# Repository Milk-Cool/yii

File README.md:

# yii
tomodachi life-style mii dolls with esp32's inside that can speak to each other via BLE and TTS!

## how do i use it?
first, you need to build the dolls!! you can find the pcb files and the schematic under the `kicad/` directory, or you can take a look at them here:

note that even though i'd recommend a pcb, it's not really necessary to use a pcb since all the components are held together by plush anyway. you can also see a list of components in `bom.csv`.\
as for the dolls themselves, go creative! i found [these on aliexpress](https://www.aliexpress.us/item/3256811798258951.html), and dyed them with fabric paint. i also glued on velcro with fabric glue for attaching the facial features (`face/` for files to be printed), and used a zip locker so that i can open and close them to take components out when needed.

after you're done with the physical part, install the firmware on your esp32's (can be found in `firmware/`)
you can use the [online tool](https://milk-cool.github.io/yii/) to set up the dolls' name and wifi password via usb, then connect via wifi, set voice parameters and reboot to doll mode! (note: if anything goes wrong and the dolls end up bricked, you can erase the flash with esptool, google it)

as for the remote, you're gonna need a plain esp32 board. just flash it with the same firmware and set it up like you'd set up a doll, but reboot it to control mode instead. then, using the online tool, you can control your dolls (poke, feed, and play with them).

## what does it do?
there's a lot of stuff you can do with the dolls, but the most important one is watching them!! if you get two or more of them, you can watch them talk to each other. they'll develop a friendship and maybe even a romantic relationship eventually! (note: there's no gender/romantic preferences system here, everyone's attracted to everyone)

other than that, you can feed them with the remote, poke them, or play games with them. you can also track their progress and their XP as they talk to others more and more.

## why does this exist?
i was a really big fan of tomodachi life ever since i learned about the first game, and i thought i might want to bring the concept of miis to life!! and so i did :D

it's nowhere near as good, obviously, but i'm happy with the result

## credits
1p2t kicad library: https://github.com/BrianLeishman/jrgbwww24/blob/master/1P2T%20SPDT.kicad_mod
tp4056 kicad library: https://github.com/ccadic/TP4056-18650

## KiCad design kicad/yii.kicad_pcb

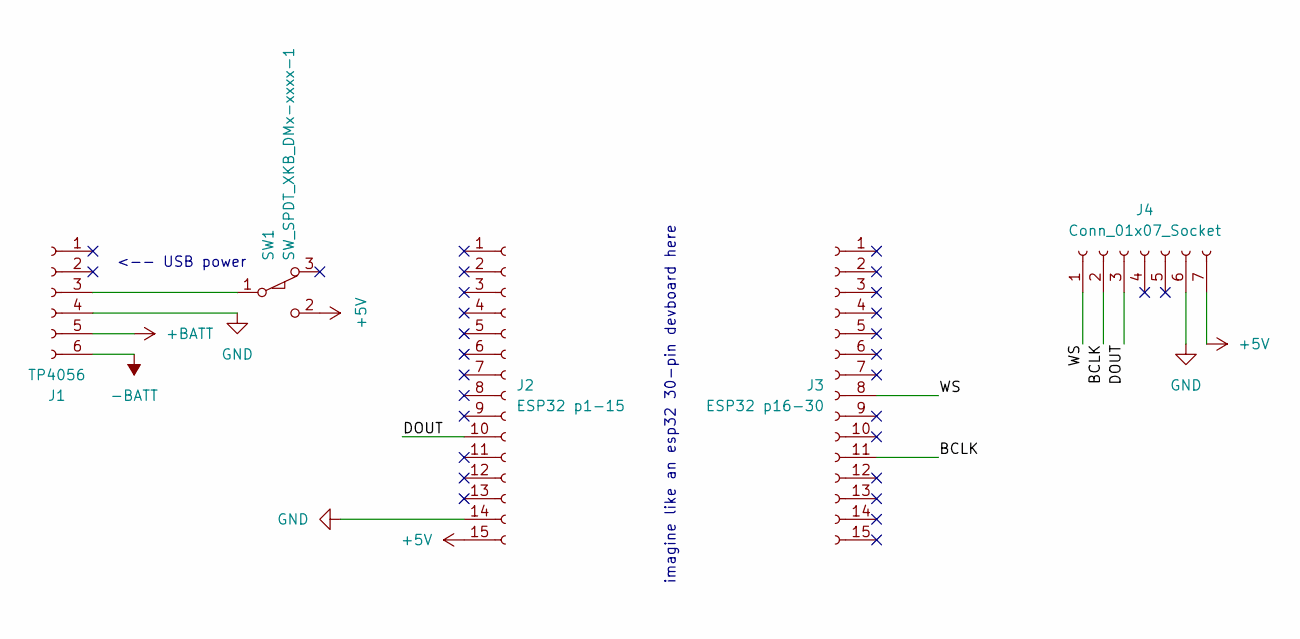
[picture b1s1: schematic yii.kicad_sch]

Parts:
J1: TP4056; TP4056-18650
J2: ESP32 p1-15; PinHeader_1x15_P2.54mm_Vertical
J3: ESP32 p16-30; PinHeader_1x15_P2.54mm_Vertical
J4: Conn_01x07_Socket; PinSocket_1x07_P2.54mm_Vertical
SW1: SW_SPDT_XKB_DMx-xxxx-1; 1p2t

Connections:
+5V: J2.15, J4.7, SW1.2 (B)
+BATT: J1.5
-BATT: J1.6
/BCLK: J3.11, J4.2
/DOUT: J2.10, J4.3
/WS: J3.8, J4.1
GND: J1.4, J2.14, J4.6
unnamed: J1.3, SW1.1 (A)

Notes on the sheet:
<-- USB power
imagine like an esp32 30-pin devboard here

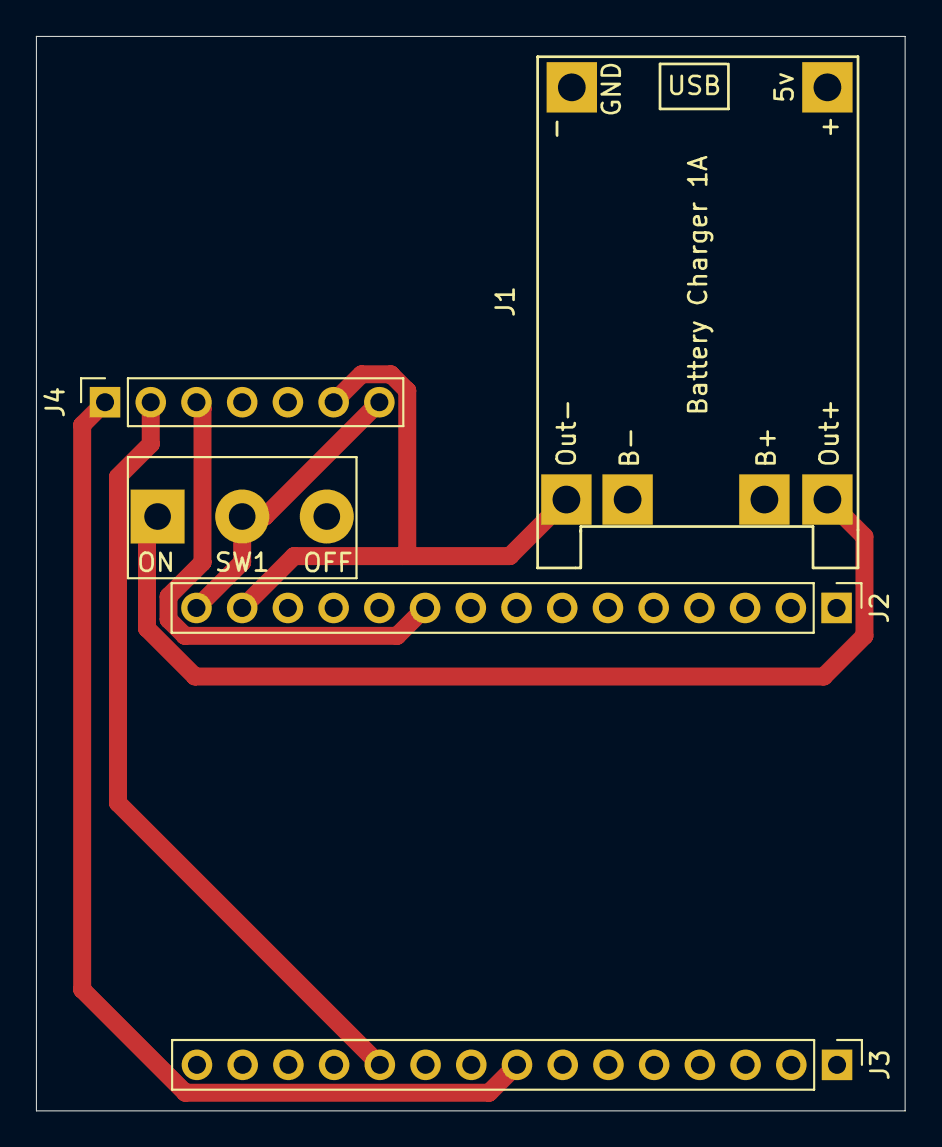
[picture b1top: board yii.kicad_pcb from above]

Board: 2 copper layers, 48.3 x 59.7 mm, 5 parts (0 on the bottom side), 6 nets.

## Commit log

2026-04-01 oopsie woopsie accidentally named a repo after an existing product
2026-04-02 i got... something
2026-04-02 voice customization
2026-04-03 bus & storage
2026-04-03 base for simple communication
2026-04-04 interactions & tts!!
2026-04-04 fix interactions protocol
2026-04-04 more dialogues & things
2026-04-04 fix relaionships storage
2026-04-05 a lot of state fixes + more dialogues
2026-04-05 use mutexes in state.cpp
2026-04-05 prevent looping random
2026-04-05 fix repeated last phrase
2026-04-05 ..but actually now
2026-04-05 made it reset the dialogue after some time
2026-04-06 more dialogue
2026-04-06 typo
2026-04-08 improve setup mode
2026-04-08 more things categories
2026-04-08 better random
2026-04-08 oops i literallyforgot to add this line
2026-04-09 becoming friends !!
2026-04-09 more ACTIVITY_TALKING dalogue
2026-04-09 proper tabulation
2026-04-09 they can now confess and become couples lol
2026-04-11 wifi config page
2026-04-12 reduce gain a bit again bc apparently it's too much for my batteries??
2026-04-12 reduce it just a little bit more
2026-04-12 eh it's just customizable now
2026-04-12 oops
2026-06-11 tamagotchi functionality
2026-06-11 a few fixes
2026-06-11 web config
2026-06-11 fix range
2026-06-11 remote control control in web panel
2026-06-11 add a control panel deployment workflow
2026-06-11 change base for vite
2026-06-12 readme, bom, and most of the necessary files
2026-06-12 OOPS miscalculation
2026-06-13 add zine and photo to the readme
